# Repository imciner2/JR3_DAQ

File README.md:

JR3_DAQ
=======

Analog Data Acquisition unit for a JR3 Force/Moment sensor.

## Requirements:
* All connections must be idiot-proof
* Sealed box, only JR3 connector, computer connector, power connector
*	Raw voltage must be recorded

## Sensor:
*	It must interface with a JR3	67M25A3-I40-AH 200N
*	That sensor requires a +-12V supply
*	That sensor provides a +-10V output

## Digital Acquisition Hardware
*	It uses a NI USB-6221 DAQ in the OEM form-factor
**	16 analog inputs
**	250kS/s
**	Labview interface
**	http://sine.ni.com/nips/cds/view/p/lang/en/nid/209809
**	34-pin ribbon cable connector

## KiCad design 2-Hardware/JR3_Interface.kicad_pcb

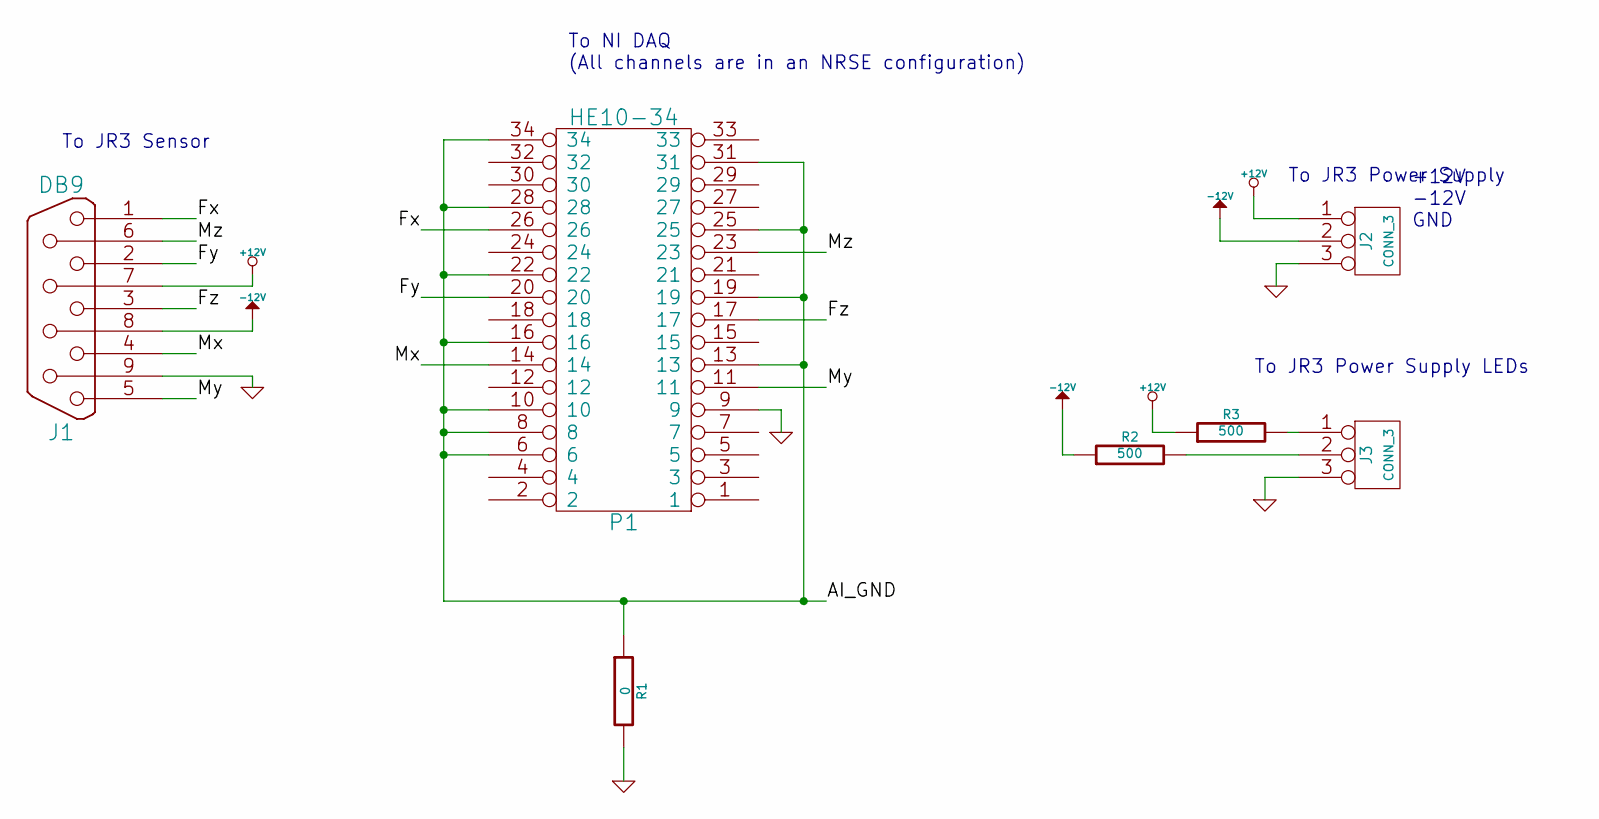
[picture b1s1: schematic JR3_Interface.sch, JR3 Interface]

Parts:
J1: DB9
J2, J3: CONN_3
P1: HE10-34
R1: 0
R2, R3: 500

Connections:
+12V: J1.7, J2.1, R3.1
-12V: J1.8, J2.2 (PM), R2.1
/AI_GND: P1.6, P1.8, P1.10, P1.13, P1.16, P1.19, P1.22, P1.25, P1.28, P1.31, P1.34, R1.1
/Fx: J1.1, P1.26
/Fy: J1.2, P1.20
/Fz: J1.3, P1.17
/Mx: J1.4, P1.14
/My: J1.5, P1.11
/Mz: J1.6, P1.23
GND: J1.9, J2.3, J3.3, P1.9, P1.12, P1.15, P1.18, P1.21, P1.24, P1.27, R1.2
unnamed: J3.1, R3.2
unnamed: J3.2 (PM), R2.2

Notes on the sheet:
To JR3 Sensor
To NI DAQ (All channels are in an NRSE configuration)
To JR3 Power Supply
To JR3 Power Supply LEDs
+12V -12V GND

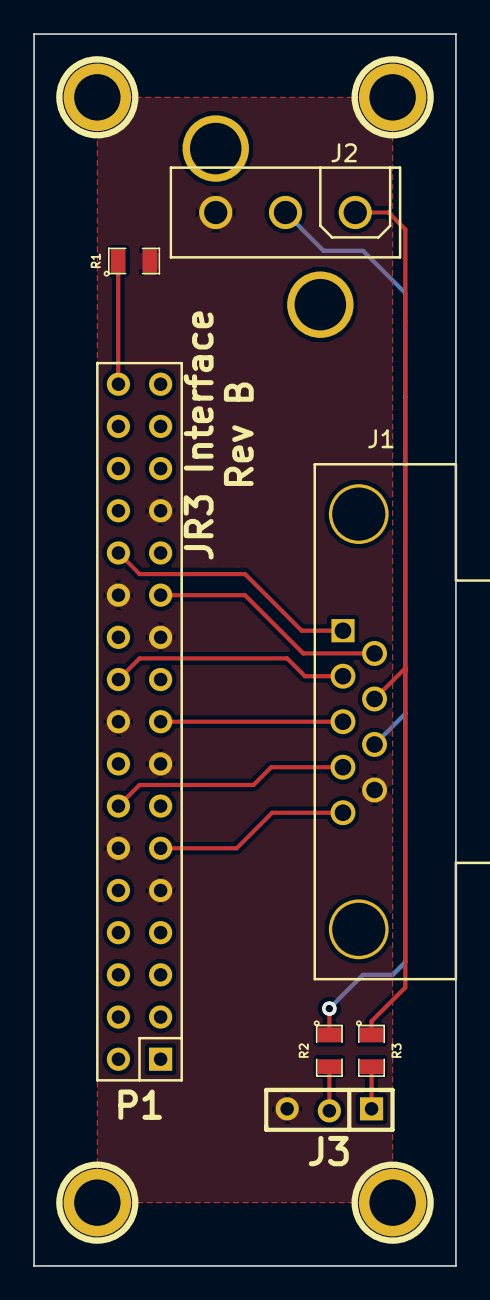
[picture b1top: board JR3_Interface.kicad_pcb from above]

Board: 2 copper layers, 25.4 x 74.2 mm, 11 parts (0 on the bottom side), 12 nets.

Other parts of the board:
1PIN, 1PIN#2, 1PIN#3, 1PIN#4: P***; 1pin

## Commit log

2014-03-31 Initial commit of the hardware files from revision A.
2014-04-16 Fixes #3.
    Adds channels AI8-AI13 to the ground plane to create differential signaling channels.
2014-04-16 Fixes #5 and resolves #3. Also fixes the power connector footprint on this board.
2014-04-16 Manufacturing files for the Rev B board.
2014-04-16 Verified the gerber files.
2014-08-10 Added gitignore file
2015-02-04 Added documentation from manufacturers
2015-02-04 Updated readme to contain more project information
2015-02-04 Update readme formatting
